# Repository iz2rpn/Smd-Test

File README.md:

# Smd-Test
Kicad software

"THE BEER-WARE LICENSE"

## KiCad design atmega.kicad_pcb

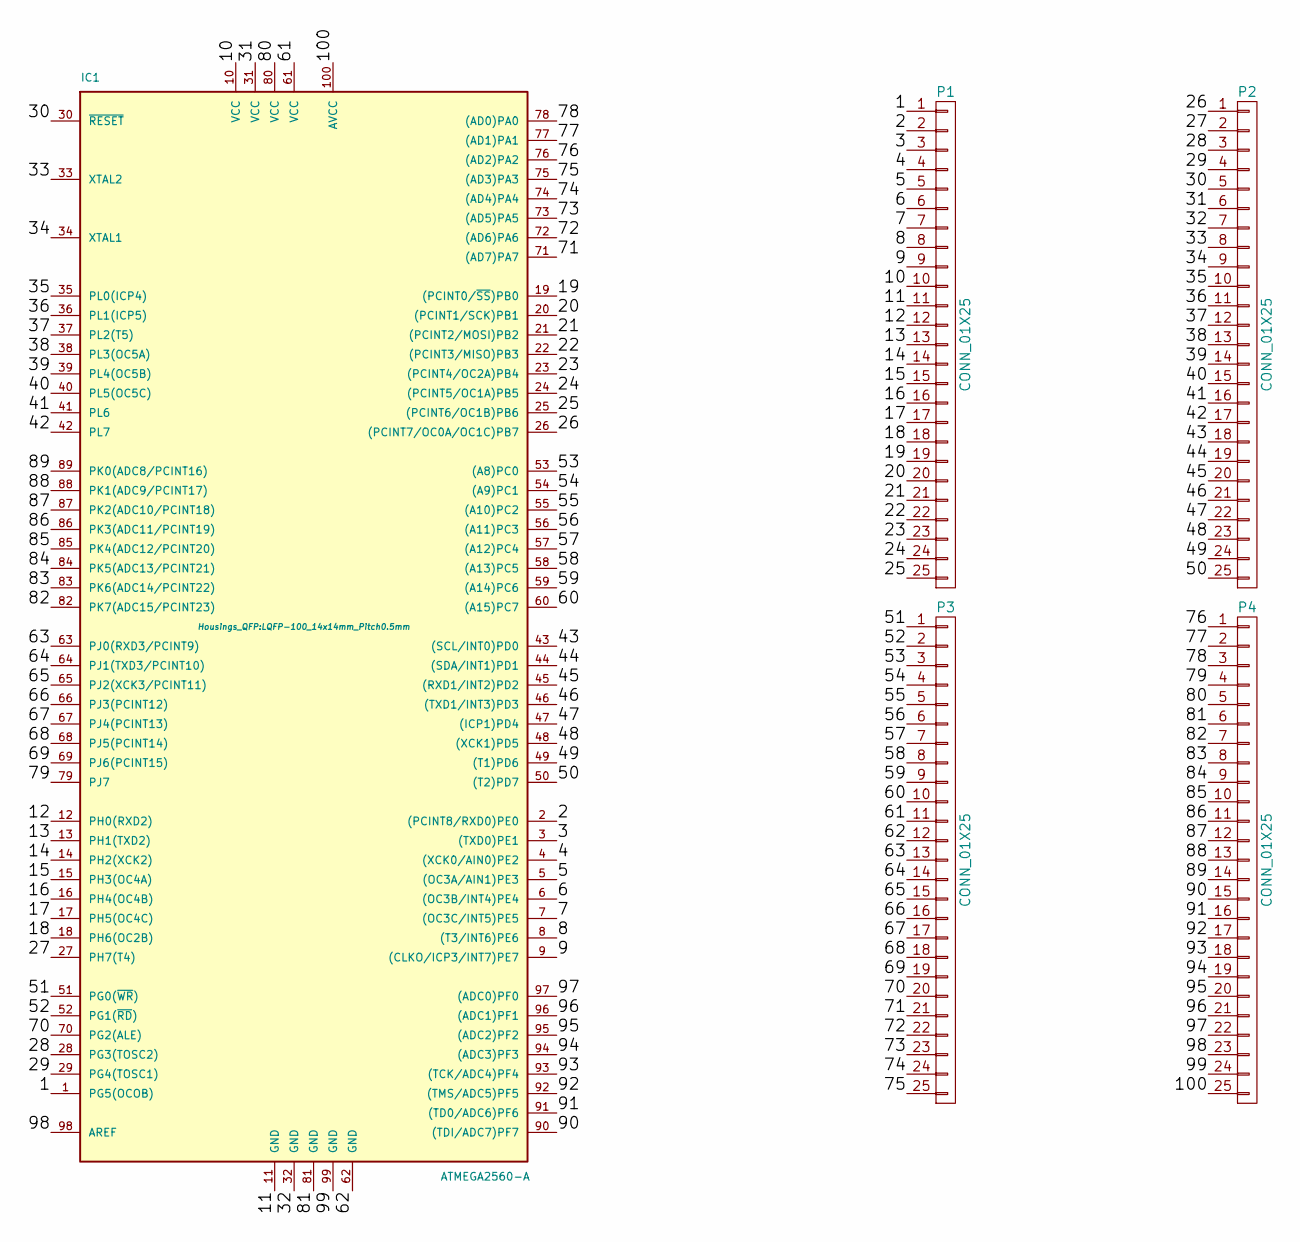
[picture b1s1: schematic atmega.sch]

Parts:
IC1: ATMEGA2560-A; LQFP-100_14x14mm_Pitch0.5mm
P1, P2, P3, P4: CONN_01X25; Pin_Header_Straight_1x25

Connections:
/1: IC1.1 (PG5(OCOB)), P1.1
/2: IC1.2 ((PCINT8/RXD0)PE0), P1.2
/3: IC1.3 ((TXD0)PE1), P1.3
/4: IC1.4 ((XCK0/AIN0)PE2), P1.4
/5: IC1.5 ((OC3A/AIN1)PE3), P1.5
/6: IC1.6 ((OC3B/INT4)PE4), P1.6
/7: IC1.7 ((OC3C/INT5)PE5), P1.7
/8: IC1.8 ((T3/INT6)PE6), P1.8
/9: IC1.9 ((CLKO/ICP3/INT7)PE7), P1.9
/10: IC1.10 (VCC), P1.10
/11: IC1.11 (GND), P1.11
/12: IC1.12 (PH0(RXD2)), P1.12
/13: IC1.13 (PH1(TXD2)), P1.13
/14: IC1.14 (PH2(XCK2)), P1.14
/15: IC1.15 (PH3(OC4A)), P1.15
/16: IC1.16 (PH4(OC4B)), P1.16
/17: IC1.17 (PH5(OC4C)), P1.17
/18: IC1.18 (PH6(OC2B)), P1.18
/19: IC1.19 ((PCINT0/~SS~)PB0), P1.19
/20: IC1.20 ((PCINT1/SCK)PB1), P1.20
/21: IC1.21 ((PCINT2/MOSI)PB2), P1.21
/22: IC1.22 ((PCINT3/MISO)PB3), P1.22
/23: IC1.23 ((PCINT4/OC2A)PB4), P1.23
/24: IC1.24 ((PCINT5/OC1A)PB5), P1.24
/25: IC1.25 ((PCINT6/OC1B)PB6), P1.25
/26: IC1.26 ((PCINT7/OC0A/OC1C)PB7), P2.1
/27: IC1.27 (PH7(T4)), P2.2
/28: IC1.28 (PG3(TOSC2)), P2.3
/29: IC1.29 (PG4(TOSC1)), P2.4
/30: IC1.30 (~RESET), P2.5
/31: IC1.31 (VCC), P2.6
/32: IC1.32 (GND), P2.7
/33: IC1.33 (XTAL2), P2.8
/34: IC1.34 (XTAL1), P2.9
/35: IC1.35 (PL0(ICP4)), P2.10
/36: IC1.36 (PL1(ICP5)), P2.11
/37: IC1.37 (PL2(T5)), P2.12
/38: IC1.38 (PL3(OC5A)), P2.13
/39: IC1.39 (PL4(OC5B)), P2.14
/40: IC1.40 (PL5(OC5C)), P2.15
/41: IC1.41 (PL6), P2.16
/42: IC1.42 (PL7), P2.17
/43: IC1.43 ((SCL/INT0)PD0), P2.18
/44: IC1.44 ((SDA/INT1)PD1), P2.19
/45: IC1.45 ((RXD1/INT2)PD2), P2.20
/46: IC1.46 ((TXD1/INT3)PD3), P2.21
/47: IC1.47 ((ICP1)PD4), P2.22
/48: IC1.48 ((XCK1)PD5), P2.23
/49: IC1.49 ((T1)PD6), P2.24
/50: IC1.50 ((T2)PD7), P2.25
/51: IC1.51 (PG0(~WR~)), P3.1
/52: IC1.52 (PG1(~RD~)), P3.2
/53: IC1.53 ((A8)PC0), P3.3
/54: IC1.54 ((A9)PC1), P3.4
/55: IC1.55 ((A10)PC2), P3.5
/56: IC1.56 ((A11)PC3), P3.6
/57: IC1.57 ((A12)PC4), P3.7
/58: IC1.58 ((A13)PC5), P3.8
/59: IC1.59 ((A14)PC6), P3.9
/60: IC1.60 ((A15)PC7), P3.10
/61: IC1.61 (VCC), P3.11
/62: IC1.62 (GND), P3.12
/63: IC1.63 (PJ0(RXD3/PCINT9)), P3.13
/64: IC1.64 (PJ1(TXD3/PCINT10)), P3.14
/65: IC1.65 (PJ2(XCK3/PCINT11)), P3.15
/66: IC1.66 (PJ3(PCINT12)), P3.16
/67: IC1.67 (PJ4(PCINT13)), P3.17
/68: IC1.68 (PJ5(PCINT14)), P3.18
/69: IC1.69 (PJ6(PCINT15)), P3.19
/70: IC1.70 (PG2(ALE)), P3.20
/71: IC1.71 ((AD7)PA7), P3.21
/72: IC1.72 ((AD6)PA6), P3.22
/73: IC1.73 ((AD5)PA5), P3.23
/74: IC1.74 ((AD4)PA4), P3.24
/75: IC1.75 ((AD3)PA3), P3.25
/76: IC1.76 ((AD2)PA2), P4.1
/77: IC1.77 ((AD1)PA1), P4.2
/78: IC1.78 ((AD0)PA0), P4.3
/79: IC1.79 (PJ7), P4.4
/80: IC1.80 (VCC), P4.5
/81: IC1.81 (GND), P4.6
/82: IC1.82 (PK7(ADC15/PCINT23)), P4.7
/83: IC1.83 (PK6(ADC14/PCINT22)), P4.8
/84: IC1.84 (PK5(ADC13/PCINT21)), P4.9
/85: IC1.85 (PK4(ADC12/PCINT20)), P4.10
/86: IC1.86 (PK3(ADC11/PCINT19)), P4.11
/87: IC1.87 (PK2(ADC10/PCINT18)), P4.12
/88: IC1.88 (PK1(ADC9/PCINT17)), P4.13
/89: IC1.89 (PK0(ADC8/PCINT16)), P4.14
/90: IC1.90 ((TDI/ADC7)PF7), P4.15
/91: IC1.91 ((TD0/ADC6)PF6), P4.16
/92: IC1.92 ((TMS/ADC5)PF5), P4.17
/93: IC1.93 ((TCK/ADC4)PF4), P4.18
/94: IC1.94 ((ADC3)PF3), P4.19
/95: IC1.95 ((ADC2)PF2), P4.20
/96: IC1.96 ((ADC1)PF1), P4.21
/97: IC1.97 ((ADC0)PF0), P4.22
/98: IC1.98 (AREF), P4.23
/99: IC1.99 (GND), P4.24
/100: IC1.100 (AVCC), P4.25

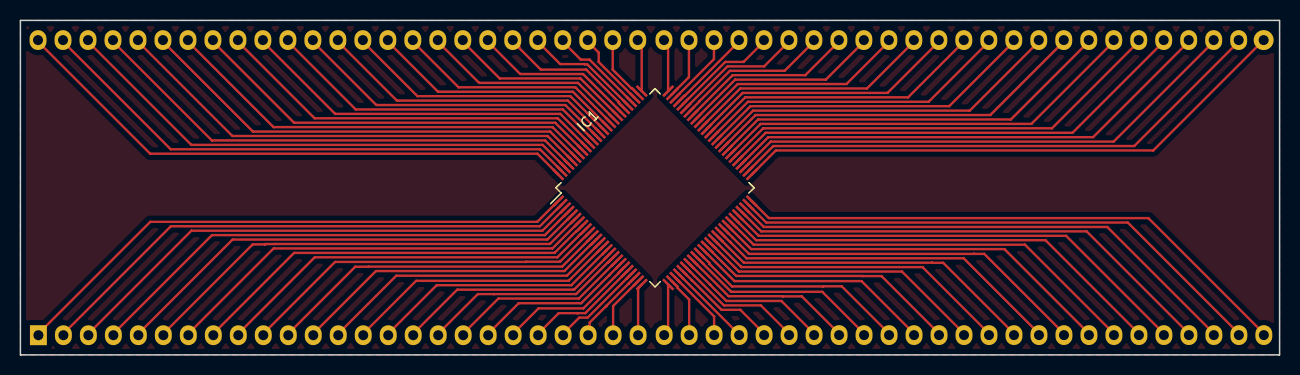
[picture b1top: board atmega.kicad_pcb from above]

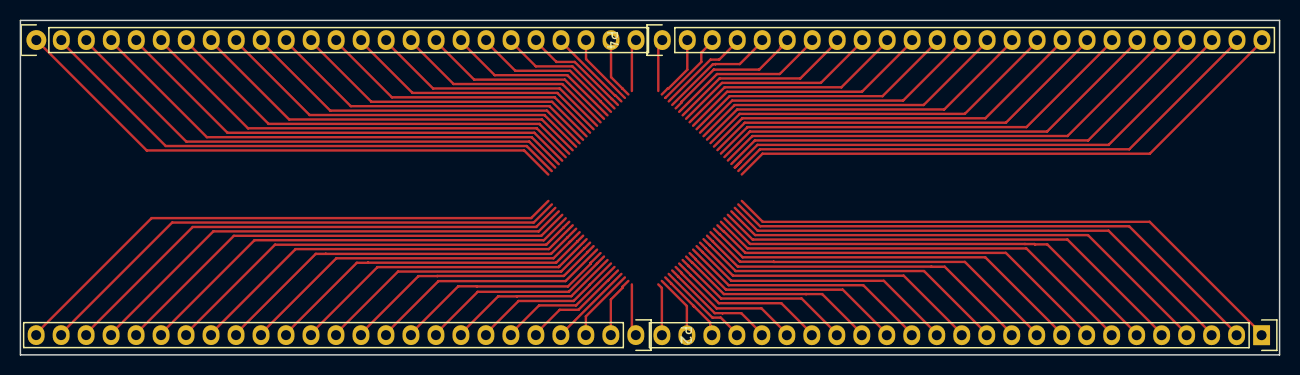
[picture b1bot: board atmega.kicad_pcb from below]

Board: 2 copper layers, 128.0 x 34.0 mm, 5 parts (4 on the bottom side), 100 nets.
